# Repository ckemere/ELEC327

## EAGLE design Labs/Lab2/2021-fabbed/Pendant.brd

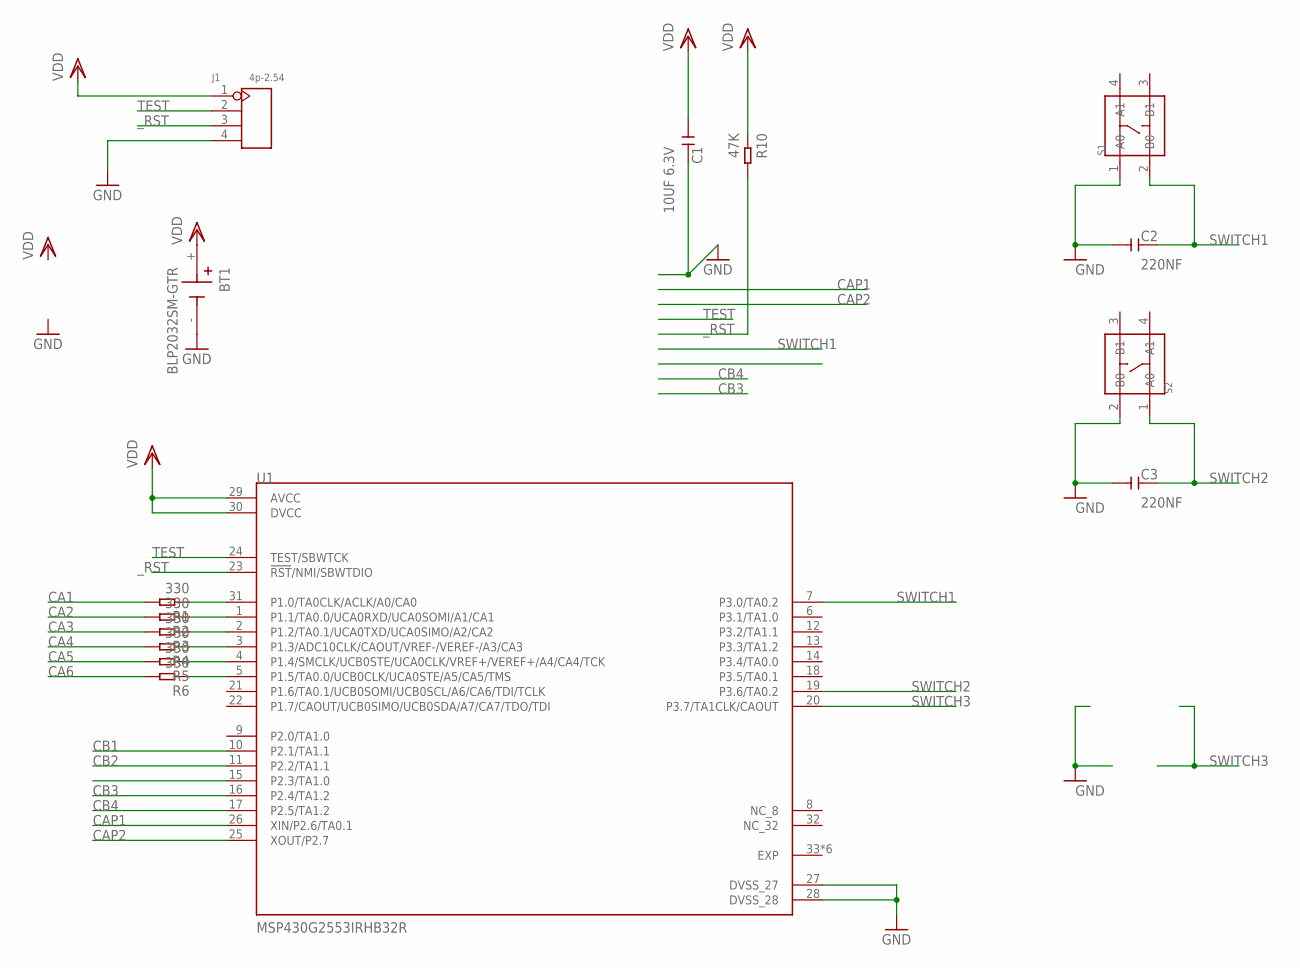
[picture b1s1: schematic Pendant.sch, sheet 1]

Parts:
BT1: BLP2032SM-GTR; BAT_BLP2032SM-GTR
C1: 10UF 6.3V; C0603
C2, C3: 220NF; C0402
J1: 4p-2.54; H4-2.54
R1, R2, R3, R4, R5, R6: 330; R0805
R10: 47K; R0603
S1, S2: SMD-SWITCH-TACTILE-SPST-NO(4P-D6.0MM); SW4-SMD-6.0X6.0X5.0MM
U1: MSP430G2553IRHB32R; IC_MSP430G2553IRHB32R

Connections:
CA1: R1.2; also elsewhere on the board
CA2: R2.2; also elsewhere on the board
CA3: R3.2; also elsewhere on the board
CA4: R4.2; also elsewhere on the board
CA5: R5.2; also elsewhere on the board
CA6: R6.2; also elsewhere on the board
CAP1: U1.26 (XIN/P2.6/TA0.1)
CAP2: U1.25 (XOUT/P2.7)
CB1: U1.10 (P2.1/TA1.1); also elsewhere on the board
CB2: U1.11 (P2.2/TA1.1); also elsewhere on the board
CB3: U1.16 (P2.4/TA1.2); also elsewhere on the board
CB4: U1.17 (P2.5/TA1.2); also elsewhere on the board
GND: BT1.-, C1.2, C2.1, C3.1, J1.4, S1.1 (A0), S2.2 (B0), U1.27 (DVSS_27), U1.28 (DVSS_28)
unnamed: R1.1, U1.31 (P1.0/TA0CLK/ACLK/A0/CA0)
unnamed: R2.1, U1.1 (P1.1/TA0.0/UCA0RXD/UCA0SOMI/A1/CA1)
unnamed: R3.1, U1.2 (P1.2/TA0.1/UCA0TXD/UCA0SIMO/A2/CA2)
unnamed: R4.1, U1.3 (P1.3/ADC10CLK/CAOUT/VREF-/VEREF-/A3/CA3)
unnamed: R5.1, U1.4 (P1.4/SMCLK/UCB0STE/UCA0CLK/VREF+/VEREF+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)
unnamed: R6.1, U1.5 (P1.5/TA0.0/UCB0CLK/UCA0STE/A5/CA5/TMS)
SWITCH1: C2.2, S1.2 (B0), U1.7 (P3.0/TA0.2)
SWITCH2: C3.2, S2.1 (A0), U1.19 (P3.6/TA0.2)
SWITCH3: U1.20 (P3.7/TA1CLK/CAOUT)
TEST: J1.2, U1.24 (TEST/SBWTCK)
VDD: BT1.+, C1.1, J1.1, R10.1, U1.29 (AVCC), U1.30 (DVCC)
_RST: J1.3, R10.2, U1.23 (!RST!/NMI/SBWTDIO)

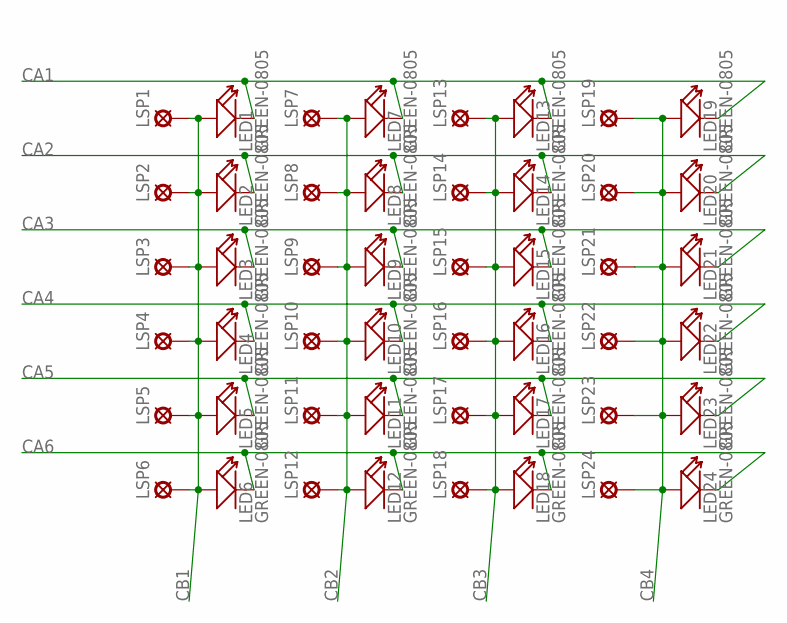
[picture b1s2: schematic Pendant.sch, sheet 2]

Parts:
LED1, LED2, LED3, LED4, LED5, LED6, LED7, LED8, LED9, LED10, LED11, LED12, LED13, LED14, LED15, LED16, LED17, LED18, LED19, LED20, LED21, LED22, LED23, LED24: GREEN-0805; LED-0805
LSP1, LSP2, LSP3, LSP4, LSP5, LSP6, LSP7, LSP8, LSP9, LSP10, LSP11, LSP12, LSP13, LSP14, LSP15, LSP16, LSP17, LSP18, LSP19, LSP20, LSP21, LSP22, LSP23, LSP24: LSP10

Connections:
CA1: LED1.-, LED7.-, LED13.-, LED19.-; also elsewhere on the board
CA2: LED2.-, LED8.-, LED14.-, LED20.-; also elsewhere on the board
CA3: LED3.-, LED9.-, LED15.-, LED21.-; also elsewhere on the board
CA4: LED4.-, LED10.-, LED16.-, LED22.-; also elsewhere on the board
CA5: LED5.-, LED11.-, LED17.-, LED23.-; also elsewhere on the board
CA6: LED6.-, LED12.-, LED18.-, LED24.-; also elsewhere on the board
CB1: LED1.+, LED2.+, LED3.+, LED4.+, LED5.+, LED6.+, LSP1.MP, LSP2.MP, LSP3.MP, LSP4.MP, LSP5.MP, LSP6.MP; also elsewhere on the board
CB2: LED7.+, LED8.+, LED9.+, LED10.+, LED11.+, LED12.+, LSP7.MP, LSP8.MP, LSP9.MP, LSP10.MP, LSP11.MP, LSP12.MP; also elsewhere on the board
CB3: LED13.+, LED14.+, LED15.+, LED16.+, LED17.+, LED18.+, LSP13.MP, LSP14.MP, LSP15.MP, LSP16.MP, LSP17.MP, LSP18.MP; also elsewhere on the board
CB4: LED19.+, LED20.+, LED21.+, LED22.+, LED23.+, LED24.+, LSP19.MP, LSP20.MP, LSP21.MP, LSP22.MP, LSP23.MP, LSP24.MP; also elsewhere on the board

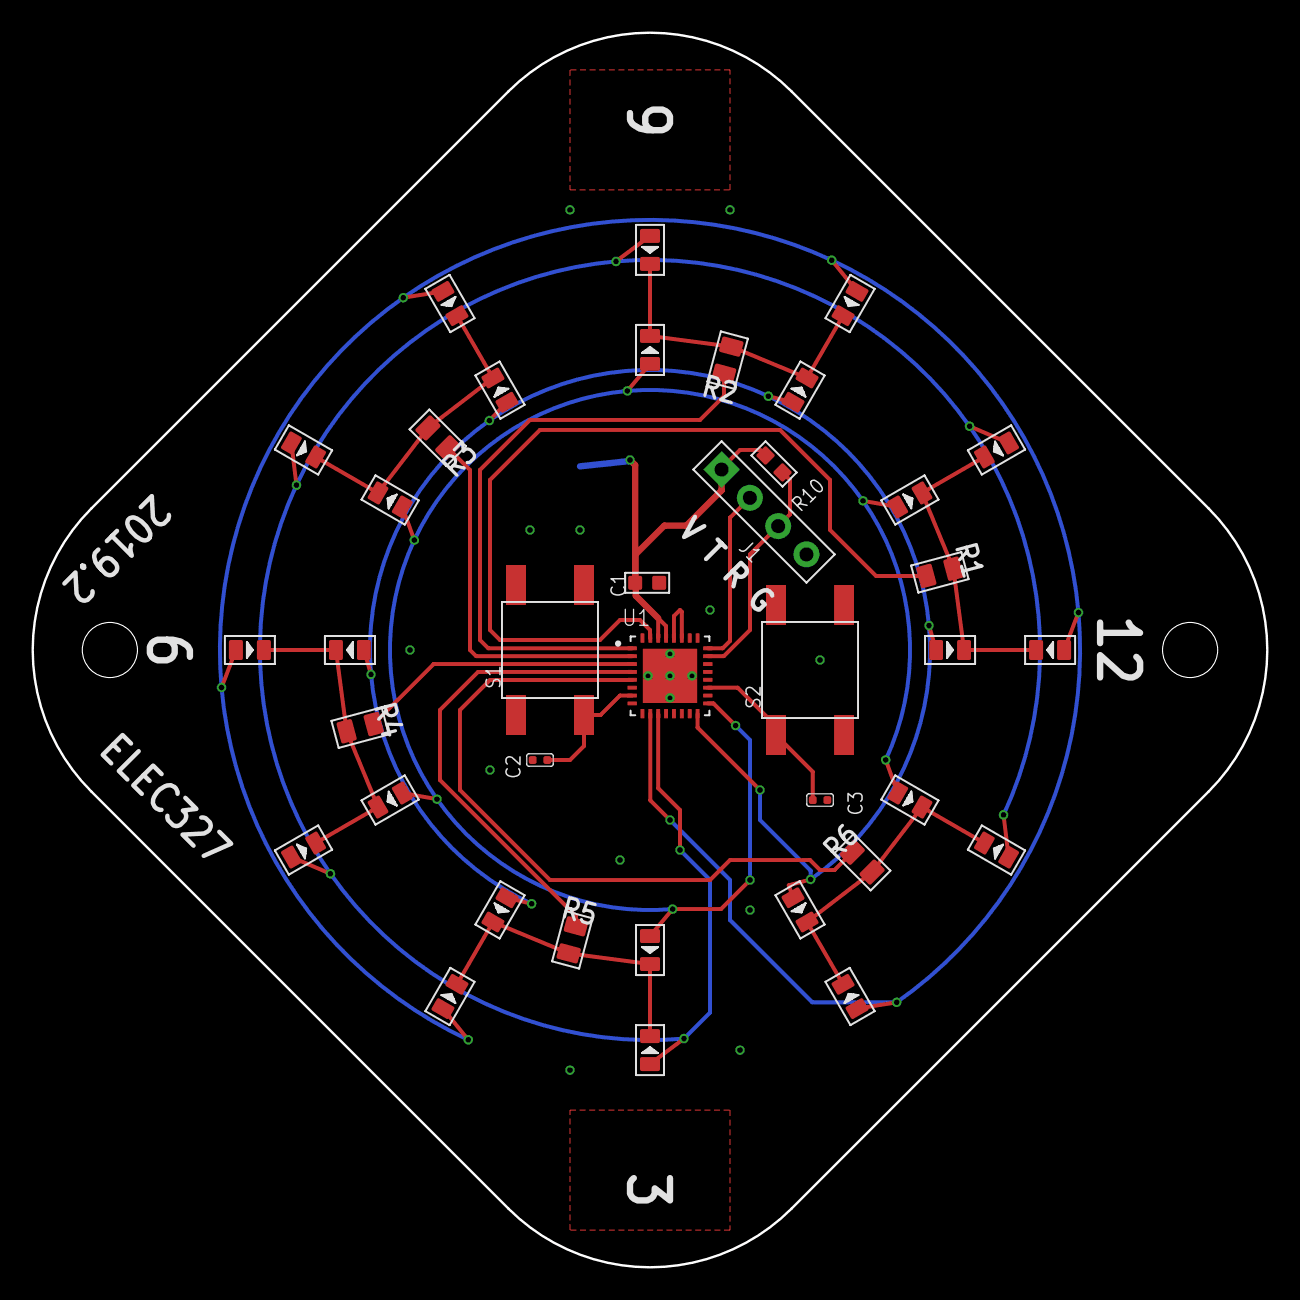
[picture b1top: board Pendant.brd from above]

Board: 2 copper layers, 78.4 x 78.4 mm, 63 parts (1 on the bottom side), 22 nets.

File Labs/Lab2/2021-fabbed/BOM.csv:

Designator,MPN,Qty,Value,Link
C1,CC0603MRX5R5BB106,1,10UF 6.3V,OPL – 302010286
"R1, R2, R3, R4, R5, R6",RC0805FR-07330RL,6,330R,OPL – 301010364
"C2, C3, C4",CC0402KRX7R7BB224,3,220NF,OPL – 302010051
R10,RC0603JR-0747KL,1,47K,OPL – 301010084
J1,P125-1104A0BS116A1,1,4p-2.54,OPL – 320020017
"S1, S2, S3",DTSM-62K-S-V-T/R(SN431),3,B3U-1000P-2P-SMD,OPL – 311020004
"LED1, LED2, LED3, LED4, LED5, LED6, LED7, LED8, LED9, LED10, LED11, LED12, LED13, LED14, LED15, LED16, LED17, LED18, LED19, LED20, LED21, LED22, LED23, LED24",17-215SYGC/S530-E2/TR8,24,GREEN-0805,OPL – 304090057
U1,MSP430G2553IRHB32R,1,MSP430G2553IRHB32R,https://www.digikey.com/en/products/detail/texas-instruments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
BT1,BS-08-B3AA0012,1,,OPL-320170005

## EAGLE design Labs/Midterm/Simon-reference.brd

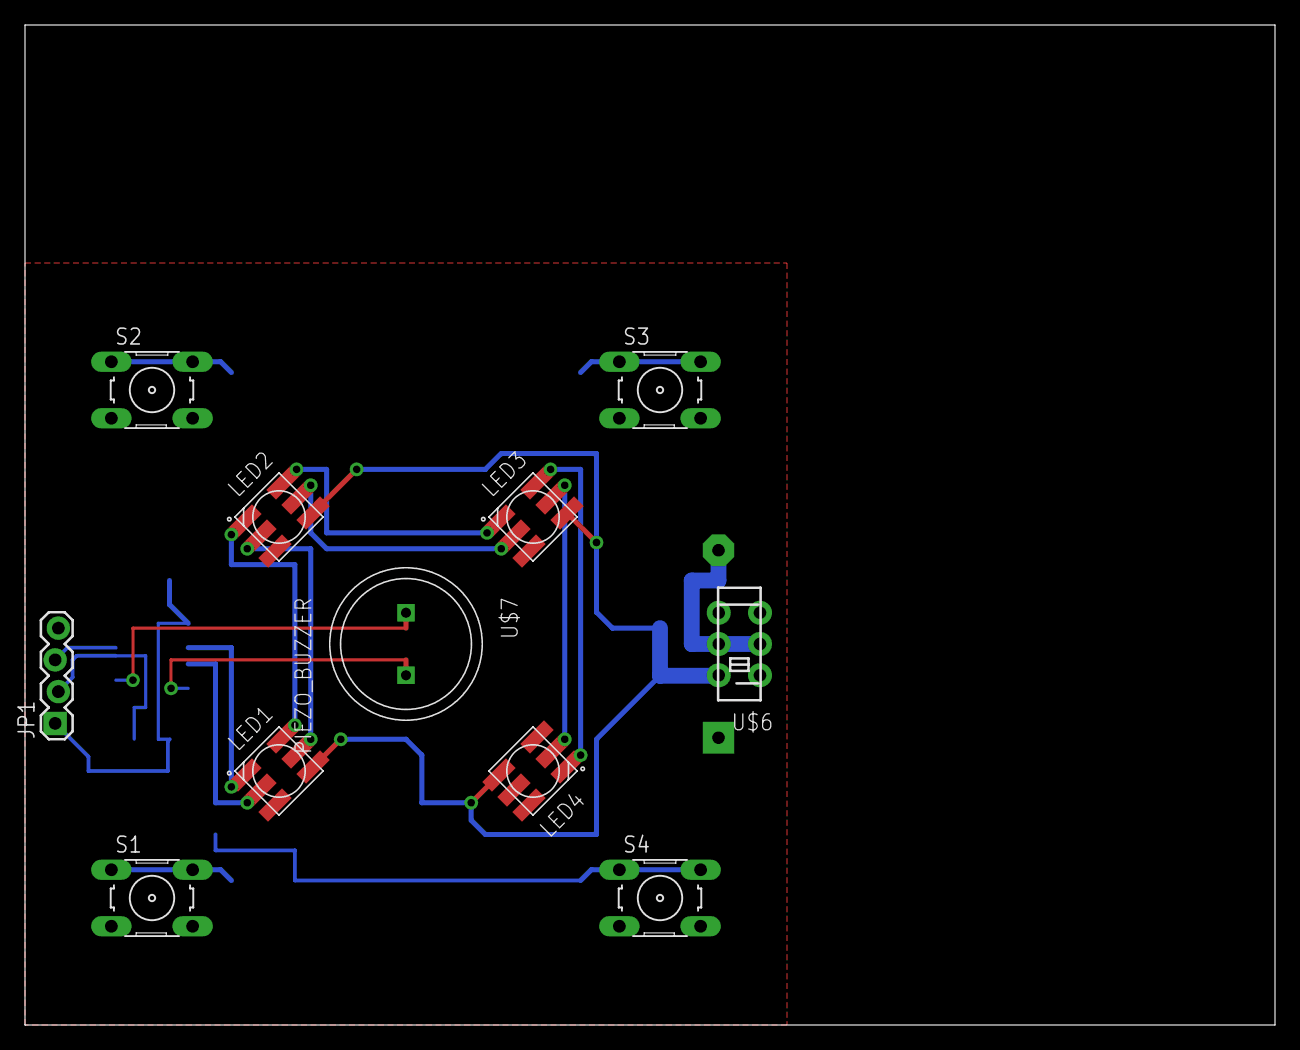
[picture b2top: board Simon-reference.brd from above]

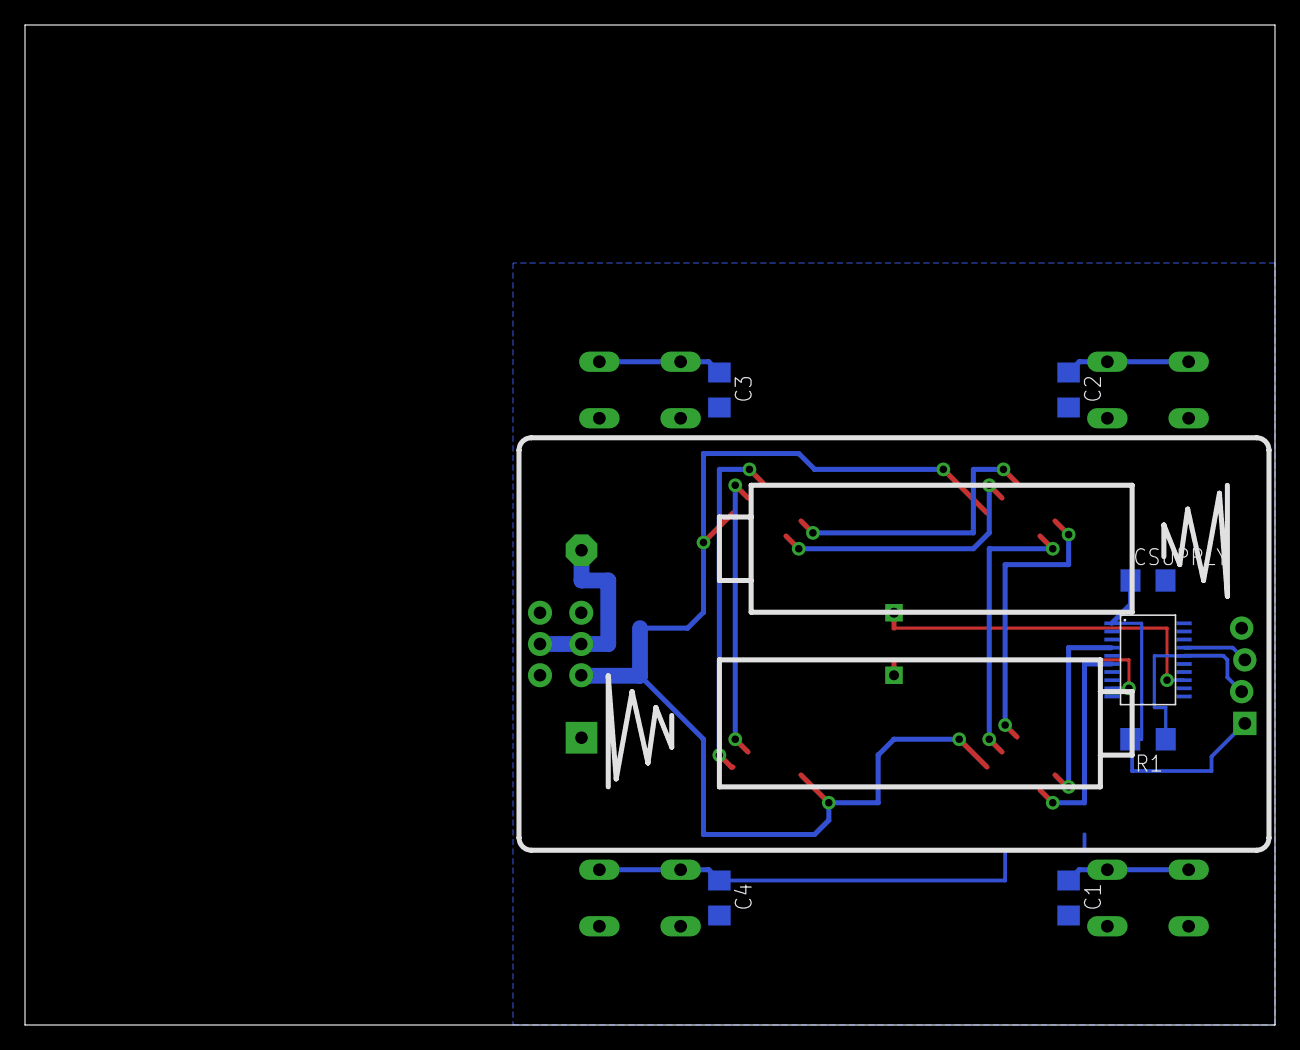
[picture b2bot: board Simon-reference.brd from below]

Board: 2 copper layers, 100.0 x 80.0 mm, 19 parts (8 on the bottom side), 19 nets.

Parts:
BAT1: BATTERY_PACK_2AA
C1, C2, C3, C4: C1206
CSUPPLY: C1206
JP1: 1X04_LOCK
LED1, LED2, LED3, LED4: APA102; 5050
R1: R1206
S1, S2, S3, S4: B3F-10XX
U$1: MSP430G2XX3TSSOP; PW20
U$6: SWITCH_DPDT; JS_DPDT_TH
U$7: PIEZO_BUZZER

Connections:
BAT_VCC: BAT1.3V, U$6.2, U$6.5
GND: BAT1.GND, C1.2, C2.2, C3.2, C4.2, CSUPPLY.2, JP1.4, LED1.3, LED2.3, LED3.3, LED4.3, S1.3, S1.4, S2.3, S2.4, S3.3, S3.4, S4.3, S4.4, U$1.20
unnamed: LED1.6, LED2.1
unnamed: LED1.5, LED2.2
unnamed: LED2.6, LED3.1
unnamed: LED2.5, LED3.2
unnamed: LED3.6, LED4.1
unnamed: LED3.5, LED4.2
unnamed: LED1.1, U$1.4
unnamed: LED1.2, U$1.6
unnamed: U$1.9, U$7.P$2
unnamed: U$1.13, U$7.P$1
unnamed: C1.1, S1.1, S1.2, U$1.8
unnamed: C2.1, S2.1, S2.2, U$1.10
unnamed: C3.1, S3.1, S3.2, U$1.11
unnamed: C4.1, S4.1, S4.2, U$1.12
RST: JP1.2, R1.1, U$1.16
TEST: JP1.3, U$1.17
VCC: CSUPPLY.1, JP1.1, LED1.4, LED2.4, LED3.4, LED4.4, R1.2, U$1.1, U$6.1, U$6.4

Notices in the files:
parts and their libraries:
SparkFun-Switches: Licensing: Creative Commons ShareAlike 4.0 International - https://creativecommons.org/licenses/by-sa/4.0
SparkFun: Licensing: CC v3.0 Share-Alike You are welcome to use this library for commercial purposes.
